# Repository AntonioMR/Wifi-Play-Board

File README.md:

# Wifi-Play-Board
Placa de experimentacion para el ESP12F (ESP8266)

## Imagenes
Cara superior

Cara inferior

## Lista de materiales
Refencias | Valor | Total Uds  | Proveedor | ref. Proveedor
----------|-------|------------|-----------|---------------
| R1, R2, R8, R9 | Resistencia 470 Ohm 0805 | 4 | TME | RC0805FR-07470R
| R26, R27, R28, R31, R32, R33, R34, R65, R66, R67 | Resistencia 120 Ohm 0805 | 10 | TME | CRCW0805120RFKTABC
| R38, R49, R51, R62, R63, R64 | Resistencia 220 Ohm 0805 | 6 | TME | RC0805FR-07220R
| R43, R44, R45, R46, R68, R69, R70, R71 | Resistencia 1 MOhm 0805 | 8 | TME | CRCW080510K0FKEA
| R21, R22, R23, R24, R25, R48, R54 | Resistencia 1 KOhm 0805 | 7 | TME | CRCW08051K00FKEA
| R12, R13, R14, R15 | Resistencia 4,7 KOhm 0805 | 4 | TME | CRCW08054K70FKEA
| R29, R30, R35, R36, R37, R50, R52, R55, R72 | Resistencia 47 KOhm 0805 | 9 | TME | CRCW080547K0FKEA
| R10, R11, R16, R17, R18, R19, R20, R3, R39, R4, R40, R41, R42, R5, R53, R56, R59, R6, R7 | Resistencia 10 KOhm 0805 | 19 | TME | CRCW080510K0FKEA
| R60, R61 | Resistencia 22 Ohm 0805 | 2 | TME | CRCW080522R0FKEA
| R57 | Resistencia 976 KOhm 0805 | 1 | RS | 708-7023
| R58 | Resistencia 309 KOhm 0805 | 1 | RS | 708-6871
| C1, C14, C15, C20, C34, C4 | Condensador cerámico 4,7 uF 1206 | 6 | TME | CL31F475ZOFNNNE
| C10 | Condensador cerámico 470 pF 0805 | 1 | TME | CL21B471KBANNND
| C11 | Condensador cerámico 100 uF 1206 | 1 | TME | CL31A107MQHNNNE
| C12, C13, C16, C17, C18, C19, C2, C21, C29, C30, C32, C8, C9 | Condensador cerámico 100 nF 0805 | 13 | TME | CL21B104KBCNNNC
| C22, C23, C24, C25 | Condensador cerámico 1 nF 0805 | 4 | TME | CL21B105KAFNNNE
| C3, C35, C7 | Condensador cerámico 10 uF 1206 | 3 | TME | CL31B103KBCNNNC
| C31, C33, C37 | Condensador cerámico 10 nF 0805 | 3 | TME | CL21B103JBANNNC
| C38, C39 | Condensador cerámico 47 pF 0805 | 2 | TME | CL21C470JBANNNC
| D1, D4, D5, D6, D7 | Diodo LED rojo 0805 | 5 | TME | OSR50805C1E
| D3 | Diodo schottky SOD-123 | 1 | TME | MBR0520L
| F2 | Fusible rearmable 500 mA 1812 | 1 | TME | SD050-16
| L2 | Inductor bobinado 4,7 uH | 1 | RS | 850-7445
| Led1 | LED RGB ánodo común 5mm | 1 | TME | OSTAMA5B31A
| P1 | Conector Molex Picoblade macho recto | 1 | RS | 279-9213
| P13, P14 | Conector Molex Picoblade macho recto | 2 | TME | ZL211-40KG-S
| P15 | Conector USB mini hembra | 1 | TME | MX-67503-1020
| Q1 Q2 Q5 Q6 Q7 Q8 Q9 | Transistor bipolar NPN SOT-23 | 7 | TME | SMBT3904E6327
| Q10 | Transistor bipolar NPN SOT-23 | 1 | TME | BC849CLT1G
| Q11 | Transistor Mosfet P SOT-23 | 1 | TME | NX2301P.215
| Q3, Q4 | Transistor Mosfet P SOT-23 | 1 | TME | BSS138P.215
| BZ1 | Buzzer raster 10 mm | 1 | TME | LD-BZPN-1705
| R47 | Resistencia LDR 5-10 KOhm| 1 | TME | GM4516
| RV1 | Potenciometro lineal 10 KOhm| 1 | RS | 729-3622
| SW1, SW2, SW3, SW4 | Pulsador NO | 4 | TME | DTSM31NB
| U1 | Controlador carga bateria LIPO MCP73831T SOT23-5 | 1 | RS | 738-6617
| U2 | Regulador de tension 3,3V LD1117S33TR SOT23-5 | 1 | RS | LD1117S33TR
| U3 | Conversor USB-Serie CH340G SOIC-16 | 1 |   |
| U5 | Acelerometro 3 ejes MMA7660FC DFN-10 | 1 | RS | 801-6873
| U6, U7 | Expansor GPIO I2C MCP23017 SSOP-28 | 2 | RS | 681-1128
| U8 | Expansor ADC SPI MCP3204 SOIC-14 | 1 | TME | MCP3204-CI/SL
| U9 | Driver para LED 8 canales PCA9551 TSSOP-16 | 1 | RS | 510-730
| U10 | Matriz LED 7x5 Anodo Filas | 1 | TME | KWM-20571ASB
| U11 | Inversor Schmitt trigger | 1 | TME | HEF40106BT
| U12 | Regulador Boost regulable | 1 | RS | 738-6257
| Y1 | Cristal 12 MHHz | 1 | RS | 526-6148

## Licencia
Este diseño es Software Libre; usted puede redistribuirlo y/o modificarlo bajo los términos de la "GNU General Public License" como lo publica la "FSF Free Software Foundation", o (a su elección) de cualquier versión posterior.

Este diseño es distribuido con la esperanza de que le sea útil, pero SIN NINGUNA GARANTIA; incluso sin la garantía implícita por la VENTA o EJERCICIO DE ALGUN PROPOSITO en particular. Vea la "GNU General Public License" para más detalles.

## Creditos
Los modelos 3D de los siguientes componentes están creados a partir de los modelos originales indicados a continuación:

Componente | Autor | Modelo 
-----------|-------|--------
|  |  | 
|  |  | 
|  |  |

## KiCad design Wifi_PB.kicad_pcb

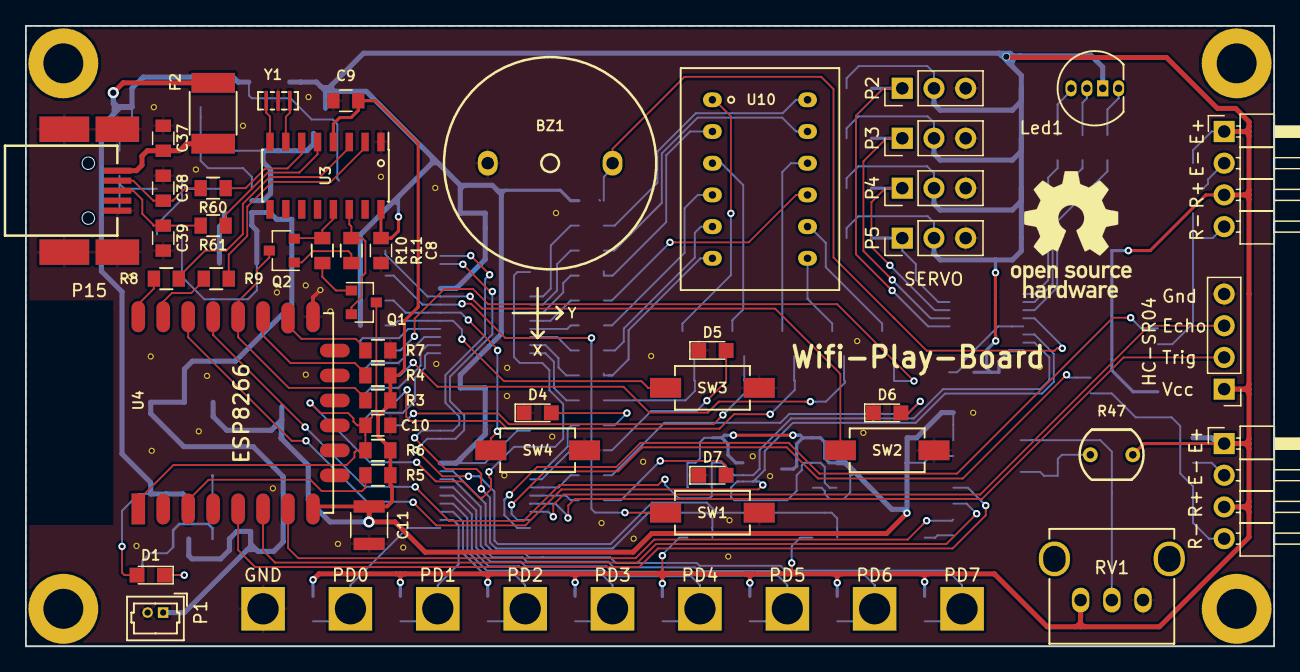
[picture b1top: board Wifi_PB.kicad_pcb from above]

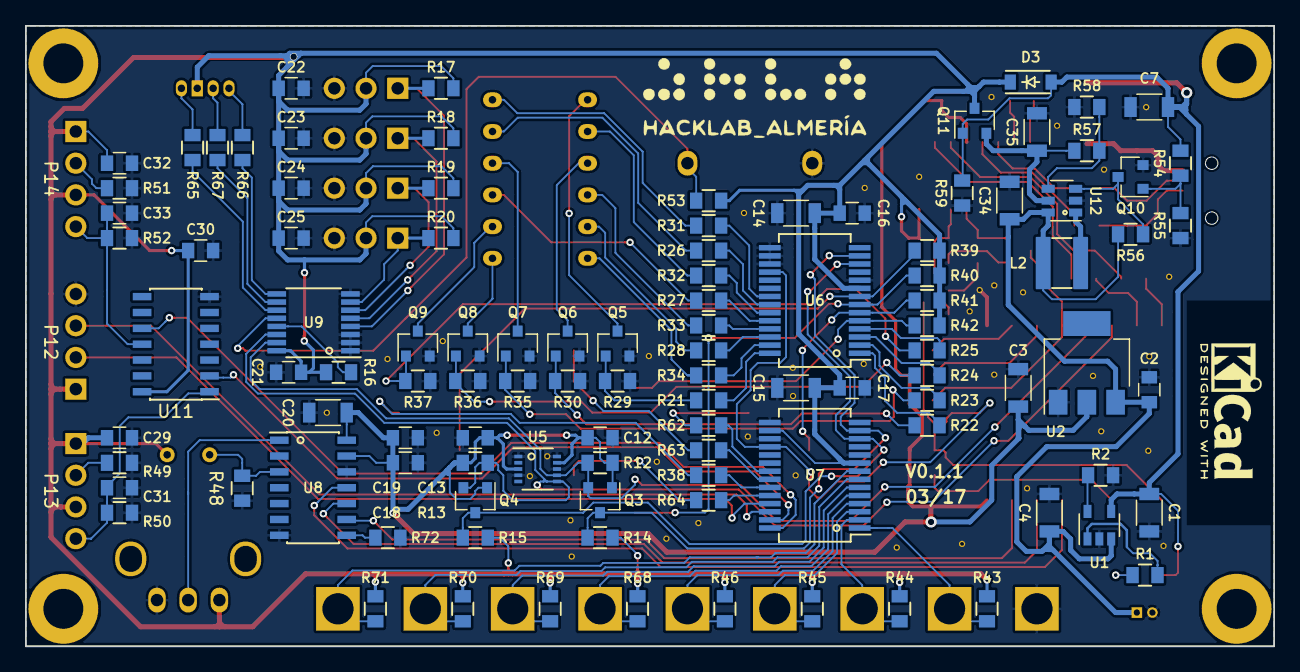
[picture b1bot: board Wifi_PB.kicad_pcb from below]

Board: 2 copper layers, 100.0 x 49.7 mm, 201 parts (106 on the bottom side), 112 nets.

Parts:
BZ1: Buzzer; LOUDITY_LD-BZPN-1705
C1, C4, C14, C15, C20, C34: 4u7; C_1206
C2, C8, C9, C12, C13, C16, C17, C18, C19, C21, C29, C30, C32: 100n; C_0805
C3, C7, C35: 10u; C_1206
C10: 0.47n; C_0805
C11: 100u; C_1210
C22, C23, C24, C25: 1u; C_0805
C31, C33, C37: 10n; C_0805
C38, C39: 0,047n; C_0805
D1, D4, D5, D6, D7: LED; LED_0805
D3: MBR0520; SOD-123
F2: F; R_1812
Gnd-Via: VAL**; Gnd-Via
Gnd-Via#2, Gnd-Via#3, Gnd-Via#4, Gnd-Via#5, Gnd-Via#6, Gnd-Via#7, Gnd-Via#8, Gnd-Via#9, Gnd-Via#10, Gnd-Via#11, Gnd-Via#12, Gnd-Via#13, Gnd-Via#14, Gnd-Via#15, Gnd-Via#16, Gnd-Via#17, Gnd-Via#18, Gnd-Via#19, Gnd-Via#20, Gnd-Via#21, Gnd-Via#22, Gnd-Via#23, Gnd-Via#24, Gnd-Via#25, Gnd-Via#26, Gnd-Via#27, Gnd-Via#28, Gnd-Via#29, Gnd-Via#30, Gnd-Via#31, Gnd-Via#32, Gnd-Via#33, Gnd-Via#34, Gnd-Via#35, Gnd-Via#36, Gnd-Via#37, Gnd-Via#38, Gnd-Via#39: VAL**; Gnd-Via
L2: 4u7; BOURNS_SRN4012T
Led1: Led_RGB; LED_RGB_5mm_G_B_COM_R_Anodo_comun
P1: CONN_01X02; Molex_PicoBlade_53047-0210_02x1.25mm_Straight
P2, P3, P4, P5: CONN_01X03; Pin_Header_Straight_1x03_Pitch2.54mm
P6, P7, P8, P9, P10, P16, P17, P18, P19: CONN_01X01; Pad_Conector_Cocodrilo
P12: CONN_01X04; Socket_Strip_Straight_1x04_Pitch2.54mm
P13, P14: CONN_01X04; Pin_Header_Angled_1x04_Pitch2.54mm
P15: USB_MINI; usb_mini_molex_675031020
Q1, Q2, Q5, Q6, Q7, Q8, Q9: SMBT3904; SOT-23
Q3, Q4: BSS138; SOT-23
Q10: BC849; SOT-23
Q11: NX2301P; SOT-23
R1, R2, R8, R9: 470; R_0805
R3, R4, R5, R6, R7, R10, R11, R16, R17, R18, R19, R20, R39, R40, R41, R42, R53, R56, R59: 10K; R_0805
R12, R13, R14, R15: 4K7; R_0805
R21, R22, R23, R24, R25, R48, R54: 1K; R_0805
R26, R27, R28, R31, R32, R33, R34, R65, R66, R67: 120; R_0805
R29, R30, R35, R36, R37, R50, R52, R55, R72: 47K; R_0805
R38, R62, R63, R64: 220; R_0805
R43, R44, R45, R46, R68, R69, R70, R71: 10M; R_0805
R47: LDR; LDR_TOKEN_PGM5_Series
R49, R51: 220R; R_0805
R57: 976K; R_0805
R58: 309K; R_0805
R60, R61: 22R; R_0805
RV1: POT; ALP_RK09K111
SW1, SW2, SW3, SW4: Pulsador_2p; CANAL_ELECTRONIC_DTSM-31N-B
U1: MCP73831T; SOT-23-5
U2: LD1117S33TR; SOT-223
U3: CH340G; SOIC-16_3.9x9.9mm_Pitch1.27mm
U4: ESP8266; ESP-12E
U5: MMA7660FC; DFN-10-1EP_3x3mm_Pitch0.5mm
U6, U7: MCP23017; SSOP-28_5.3x10.2mm_Pitch0.65mm
U8: MCP3204; SOIC-14_3.9x8.7mm_Pitch1.27mm
U9: PCA9551; TSSOP-16_4.4x5mm_Pitch0.65mm
U10: Matriz_5x7_Anodo_Filas; Matriz_Led_7X5
U11: 40106; SOIC-14_3.9x8.7mm_Pitch1.27mm
U12: MCP1640; SOT-23-6
Y1: Cristal; Murata_CSTCE_V_A

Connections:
+3V3: C3.1, C9.1, C11.1, C12.1, C13.1, C18.1, C19.1, C20.1, Q3.1, Q4.1, R3.2, R4.2, R5.2, R6.2, R12.1, R13.1, U2.2, U3.4, U4.8, U5.3, U5.9, U8.13, U8.14
+5V: C8.1, C14.1, C15.1, C16.1, C17.1, C21.1, C22.1, C23.1, C24.1, C25.1, C29.1, C30.1, C32.1, D3.1, Led1.3, P2.2, P3.2, P4.2, P5.2, P12.1, P13.1, P13.3, P14.1, P14.3, Q11.3, R14.1, R15.1, R16.1, R17.1, R18.1, R19.1, R20.1, R39.1, R40.1, R41.1, R42.1, R43.1, R44.1, R45.1, R46.1, R47.1, R53.1, R68.1, R69.1, R70.1, R71.1, RV1.1, U3.16, U6.9, U7.9, U7.16, U9.16, U11.14
/Control/EN: R5.1, U4.3
/Control/GPIO0: Q2.3, R3.1, U4.18
/Control/GPIO2: R4.1, U4.17
/Control/GPIO15: R7.1, U4.16
/Control/RxD: R9.1, U4.21
/Control/TxD: R8.1, U4.22
/Control/USBD+: R61.1, U3.5
/Control/USBD-: R60.1, U3.6
BUZZER: BZ1.1, R53.2, U9.12
CH0: RV1.2, U8.1
CH2: R47.2, R48.2, U8.3
GND: BZ1.2, C1.2, C2.2, C3.2, C4.2, C7.2, C8.2, C9.2, C10.2, C11.2, C12.2, C13.2, C14.2, C15.2, C16.2, C17.2, C18.2, C19.2, C20.2, C21.2, C22.2, C23.2, C24.2, C25.2, C29.2, C30.2, C31.2, C32.2, C33.2, C34.2, C35.2, C37.2, C38.2, C39.2, D4.1, D5.1, D6.1, D7.1, Gnd-Via.1, Gnd-Via#2.1, Gnd-Via#3.1, Gnd-Via#4.1, Gnd-Via#5.1, Gnd-Via#6.1, Gnd-Via#7.1, Gnd-Via#8.1, Gnd-Via#9.1, Gnd-Via#10.1, Gnd-Via#11.1, Gnd-Via#12.1, Gnd-Via#13.1, Gnd-Via#14.1, Gnd-Via#15.1, Gnd-Via#16.1, Gnd-Via#17.1, Gnd-Via#18.1, Gnd-Via#19.1, Gnd-Via#20.1, Gnd-Via#21.1, Gnd-Via#22.1, Gnd-Via#23.1, Gnd-Via#24.1, Gnd-Via#25.1, Gnd-Via#26.1, Gnd-Via#27.1, Gnd-Via#28.1, Gnd-Via#29.1, Gnd-Via#30.1, Gnd-Via#31.1, Gnd-Via#32.1, Gnd-Via#33.1, Gnd-Via#34.1, Gnd-Via#35.1, Gnd-Via#36.1, Gnd-Via#37.1, Gnd-Via#38.1, Gnd-Via#39.1, P1.2, P2.3, P3.3, P4.3, P5.3, P10.1, P12.4, P15.5, P15.6, Q5.2, Q6.2, Q7.2, Q8.2, Q9.2, Q10.2, R2.2, R7.2, R29.2, R30.2, R35.2, R36.2, R37.2, R48.1, R49.2, R50.2, R51.2, R52.2, R55.2, R58.2, R59.1, R72.2, RV1.3, SW1.1, SW2.1, SW3.1, SW4.1, U1.2, U2.1, U3.1, U4.15, U5.1, U5.4, U5.8, U5.10, U6.10, U6.15, U6.16, U6.17, U7.10, U7.15, U7.17, U8.7, U8.12, U9.1, U9.2, U9.3, U9.8, U11.7, U12.2, Y1.2
LED_BLUE: R67.2, U9.10
LED_GREEN: R66.2, U9.9
LED_RED: R65.2, U9.11
MISO: U4.6, U8.10
MOSI: U4.7, U8.9
unnamed: C31.1, P13.4, R50.1, U11.1
unnamed: C33.1, P14.4, R52.1, U11.11
unnamed: C37.1, F2.2, P15.1
unnamed: C38.1, P15.2, R60.2
unnamed: C39.1, P15.3, R61.2
unnamed: D1.1, R1.2
unnamed: D4.2, R62.2
unnamed: D5.2, R63.2
unnamed: D6.2, R38.2
unnamed: D7.2, R64.2
unnamed: L2.2, U12.1
unnamed: Led1.1, R66.1
unnamed: Led1.2, R67.1
unnamed: Led1.4, R65.1
unnamed: P13.2, R49.1
unnamed: P14.2, R51.1
unnamed: Q1.1, R10.1
unnamed: Q1.2, R11.2, U3.14
unnamed: Q2.1, R11.1
unnamed: Q2.2, R10.2, U3.13
unnamed: Q5.1, R21.1, R29.1
unnamed: Q5.3, U10.1
unnamed: Q6.1, R22.1, R30.1
unnamed: Q6.3, U10.3
unnamed: Q7.1, R23.1, R35.1
unnamed: Q7.3, U10.10
unnamed: Q8.1, R24.1, R36.1
unnamed: Q8.3, U10.7
unnamed: Q9.1, R25.1, R37.1
unnamed: Q9.3, U10.8
unnamed: Q10.1, R54.1, R55.1
unnamed: Q10.3, R56.1, U12.3
unnamed: R1.1, U1.1
unnamed: R2.1, U1.5
unnamed: R8.2, U3.3
unnamed: R9.2, U3.2
unnamed: R16.2, U9.13
unnamed: R26.1, U10.11
unnamed: R27.1, U10.9
unnamed: R28.1, U10.5
unnamed: R31.1, U10.12
unnamed: R32.1, U10.2
unnamed: R33.1, U10.4
unnamed: R34.1, U10.6
unnamed: R57.2, R58.1, U12.4
unnamed: R72.1, U8.8
unnamed: U3.7, Y1.1
unnamed: U3.8, Y1.3
PA0: R31.2, U6.21
PA1: R26.2, U6.22
PA2: R32.2, U6.23
PA3: R27.2, U6.24
PA4: R33.2, U6.25
PA5: R28.2, U6.26
PA6: R34.2, U6.27
PA7: R21.2, U6.28
PB0: R22.2, U6.1
PB1: R23.2, U6.2
PB2: R24.2, U6.3
PB3: R25.2, U6.4
PB4: R42.2, SW3.2, U6.5
PB5: R41.2, SW4.2, U6.6
PB6: R40.2, SW1.2, U6.7
PB7: R39.2, SW2.2, U6.8
PC0: R62.1, U7.21
PC1: R63.1, U7.22
PC2: R38.1, U7.23
PC3: R64.1, U7.24
PC4: P12.2, U7.25
PC5: P12.3, U7.26
PC6: U7.27, U11.2
PC7: U7.28, U11.10
PD0: P6.1, R43.2, U7.1
PD1: P7.1, R44.2, U7.2
PD2: P8.1, R45.2, U7.3
PD3: P9.1, R46.2, U7.4
PD4: P16.1, R68.2, U7.5
PD5: P17.1, R69.2, U7.6
PD6: P18.1, R70.2, U7.7
PD7: P19.1, R71.2, U7.8
SCK: U4.5, U8.11
SCL: Q4.2, R13.2, U4.20, U5.6, U9.14
SCL2: Q4.3, R15.2, U6.12, U7.12
SDA: Q3.2, R12.2, U4.19, U5.7, U9.15
SDA2: Q3.3, R14.2, U6.13, U7.13
SERVO1: P2.1, R17.2, U9.4
SERVO2: P3.1, R18.2, U9.5
SERVO3: P4.1, R19.2, U9.6
SERVO4: P5.1, R20.2, U9.7
V5VBOOST: C35.1, Q11.2, R57.1, U12.5
VBATT: C2.1, C4.1, C34.1, L2.1, P1.1, R56.2, U1.3, U2.3, U12.6
VUSB: C1.1, C7.1, D1.2, D3.2, F2.1, Q11.1, R54.2, R59.2, U1.4
~RESET: C10.1, Q1.3, R6.1, U4.1, U6.18, U7.18

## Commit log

2016-11-27 add .gitignore file
2017-01-15 carga inicial proyecto y hojas del esquema
2017-01-30 version preliminar de la etapa de alimentacion
2017-02-03 asignacion inicial de huellas
2017-02-04 cambiar ch340T por ch340g y añadir nc a pines
2017-02-04 cambiado cristal de cuarzo por resonador
2017-02-05 place inicial sobre la pcb
2017-02-07 ordenar componentes y referencias
2017-02-07 añadir imagenes de la pcb
2017-02-08 realizado el trazado de los reguladores
2017-02-09 modificado conexion led rgb para mejorar trazado
2017-02-12 añadida LDR. Finalizado trazado provisional
2017-02-12 añadidos logos a la serigrafia
2017-02-12 conectar reset gpio. retocar plano masa
2017-02-13 girar conector detector ultrasionidos
2017-02-13 Mejoras en serigrafia
2017-02-13 finalizada pcb V0.1
2017-02-13 ajustada margen mascara soldadura a 5 mils
2017-02-13 correcciones en serigrafias sobre pads
2017-02-13 version para envio a fabricar, gerber y panel 2x1
2017-02-13 actualizar imagenes pcb a V0.1
2017-02-15 añadidos valores y referencias a control, alimentacion y gpioEx
2017-02-16 actualizadas referencias en componentes y ordenado esquema electrico
2017-02-16 añadidas listas de resistencias al BOM
2017-02-18 añadido BOM al README
2017-02-18 añadido esquema en PDF
2017-02-19 añadidos modelos 3D y referencias relativas a estos en el proyecto
2017-02-19 error en el modelo 3d del led RGB
2017-03-03 modificada huella de U7 a SOIC14. Corrige issue #1
2017-03-12 cambiado el driver led al PCA9634
2017-03-16 errata en BOM
